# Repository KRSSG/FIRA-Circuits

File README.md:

# FIRA-Circuits
Eagle Files of FIRA Circuit

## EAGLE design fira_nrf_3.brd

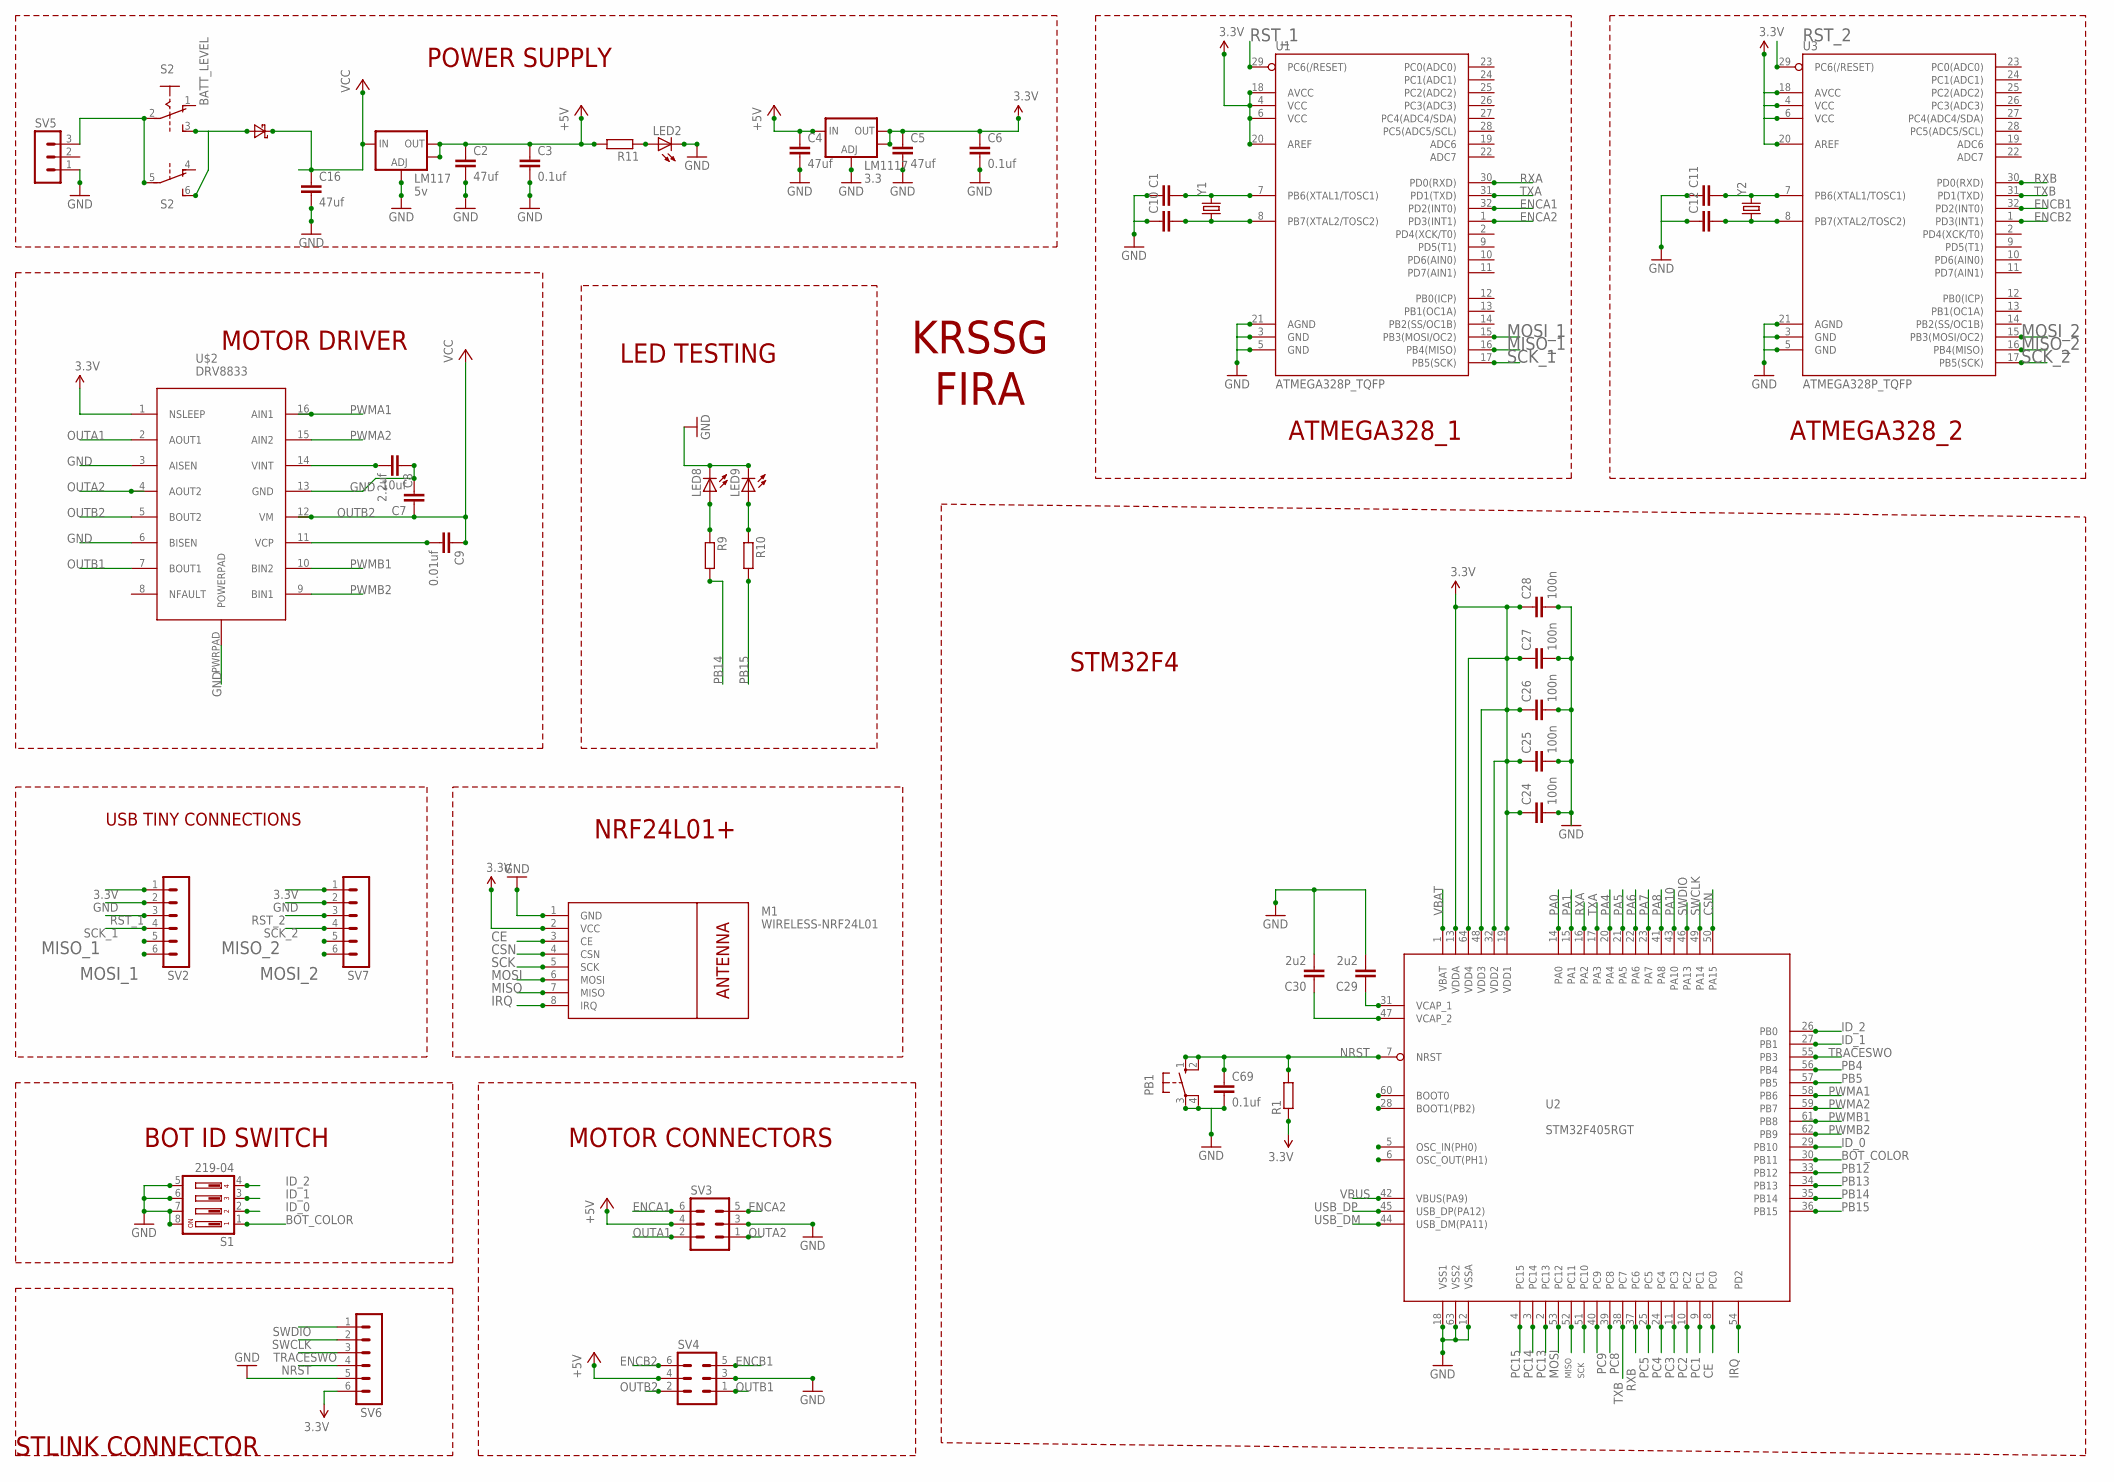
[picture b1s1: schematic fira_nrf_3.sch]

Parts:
C1, C10, C11, C12: CAP0603-CAP; 0603-CAP
C2, C4, C5, C16: 47uf; C1206
C3, C6, C69: 0.1uf; C1206
C7: 10uf; C1206
C8: 2.2uf; C1206
C9: 0.01uf; C1206
C24, C25, C26, C27, C28: 100n; 0603-CAP
C29, C30: 2u2; 0603-CAP
LED2, LED8, LED9: LEDCHIPLED_1206; CHIPLED_1206
LM117: 5v; SOT223
LM1117: 3.3; SOT223
M1: WIRELESS-NRF24L01
PB1: 10-XX; B3F-10XX
R1: R-EU_M0805; M0805
R9, R10, R11: R-EU_R1206; R1206
S1: 219-04; CTS-219-04
S2: A68-A31
SV2, SV6, SV7: MA06-1
SV3, SV4: MA03-2
SV5: MA03-1
U1, U3: ATMEGA328P_TQFP; TQFP32-08
U2: STM32F405RGT; LQFP64
U$2: DRV8833; PWP_R_PDSO_G16
VD1: IDD06SG60C; DPAK
Y1, Y2: CRYSTAL5X3; CRYSTAL-SMD-5X3

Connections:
3.3V: C5.1, C6.1, C24.1, C25.1, C26.1, C27.1, C28.1, LM1117.2 (OUT), LM1117.4 (OUT), M1.2 (VCC), R1.1, SV2.1, SV6.6, SV7.1, U1.4 (VCC), U1.6 (VCC), U1.18 (AVCC), U1.20 (AREF), U2.13 (VDDA), U2.19 (VDD1), U2.32 (VDD2), U2.48 (VDD3), U2.64 (VDD4), U3.4 (VCC), U3.6 (VCC), U3.18 (AVCC), U3.20 (AREF), U$2.1 (NSLEEP)
+5V: C2.1, C3.1, C4.1, LM117.2 (OUT), LM117.4 (OUT), LM1117.3 (IN), R11.2, SV3.4, SV4.4
BATT_LEVEL: S2.3 (S), S2.6 (S), VD1.3 (A)
BOT_COLOR: S1.1, U2.30 (PB11)
CE: M1.3 (CE), U2.8 (PC0)
CSN: M1.4 (CSN), U2.50 (PA15)
ENCA1: SV3.6, U1.32 (PD2(INT0))
ENCA2: SV3.5, U1.1 (PD3(INT1))
ENCB1: SV4.5, U3.32 (PD2(INT0))
ENCB2: SV4.6, U3.1 (PD3(INT1))
ID_0: S1.2, U2.29 (PB10)
ID_1: S1.3, U2.27 (PB1)
ID_2: S1.4, U2.26 (PB0)
IRQ: M1.8 (IRQ), U2.54 (PD2)
MISO: M1.7 (MISO), U2.52 (PC11)
MISO_1: SV2.5, U1.16 (PB4(MISO))
MISO_2: SV7.5, U3.16 (PB4(MISO))
MOSI: M1.6 (MOSI), U2.53 (PC12)
MOSI_1: SV2.6, U1.15 (PB3(MOSI/OC2))
MOSI_2: SV7.6, U3.15 (PB3(MOSI/OC2))
unnamed: LED2.A, R11.1
unnamed: LED9.A, R10.1
unnamed: C11.2, U3.7 (PB6(XTAL1/TOSC1)), Y2.3 (2)
unnamed: C8.2, U$2.14 (VINT)
unnamed: LED8.A, R9.1
unnamed: S2.2, S2.5, SV5.3
unnamed: C9.2, U$2.11 (VCP)
unnamed: C12.2, U3.8 (PB7(XTAL2/TOSC2)), Y2.1
unnamed: C29.1, U2.31 (VCAP_1)
unnamed: C30.1, U2.47 (VCAP_2)
unnamed: C1.2, U1.7 (PB6(XTAL1/TOSC1)), Y1.3 (2)
unnamed: C10.2, U1.8 (PB7(XTAL2/TOSC2)), Y1.1
NRST: C69.1, PB1.1 (S), PB1.2 (S1), R1.2, SV6.4, U2.7 (NRST)
OUTA1: SV3.2, U$2.2 (AOUT1)
OUTA2: SV3.1, U$2.4 (AOUT2)
OUTB1: SV4.1, U$2.7 (BOUT1)
OUTB2: SV4.2, U$2.5 (BOUT2)
PA0: U2.14 (PA0)
PA1: U2.15 (PA1)
PA4: U2.20 (PA4)
PA5: U2.21 (PA5)
PA6: U2.22 (PA6)
PA7: U2.23 (PA7)
PA8: U2.41 (PA8)
PA10: U2.43 (PA10)
PB4: U2.56 (PB4)
PB5: U2.57 (PB5)
PB12: U2.33 (PB12)
PB13: U2.34 (PB13)
PB14: R9.2, U2.35 (PB14)
PB15: R10.2, U2.36 (PB15)
PC1: U2.9 (PC1)
PC2: U2.10 (PC2)
PC3: U2.11 (PC3)
PC4: U2.24 (PC4)
PC5: U2.25 (PC5)
PC8: U2.39 (PC8)
PC9: U2.40 (PC9)
PC13: U2.2 (PC13)
PC14: U2.3 (PC14)
PC15: U2.4 (PC15)
PWMA1: U2.58 (PB6), U$2.16 (AIN1)
PWMA2: U2.59 (PB7), U$2.15 (AIN2)
PWMB1: U2.61 (PB8), U$2.10 (BIN2)
PWMB2: U2.62 (PB9), U$2.9 (BIN1)
RST_1: SV2.3, U1.29 (PC6(/RESET))
RST_2: SV7.3, U3.29 (PC6(/RESET))
RXA: U1.30 (PD0(RXD)), U2.16 (PA2)
RXB: U2.37 (PC6), U3.30 (PD0(RXD))
SCK: M1.5 (SCK), U2.51 (PC10)
SCK_1: SV2.4, U1.17 (PB5(SCK))
SCK_2: SV7.4, U3.17 (PB5(SCK))
SWCLK: SV6.2, U2.49 (PA14)
SWDIO: SV6.1, U2.46 (PA13)
TRACESWO: SV6.3, U2.55 (PB3)
TXA: U1.31 (PD1(TXD)), U2.17 (PA3)
TXB: U2.38 (PC7), U3.31 (PD1(TXD))
USB_DM: U2.44 (USB_DM(PA11))
USB_DP: U2.45 (USB_DP(PA12))
VBAT: U2.1 (VBAT)
VBUS: U2.42 (VBUS(PA9))
VCC: C7.1, C9.1, C16.1, LM117.3 (IN), U$2.12 (VM), VD1.2 (C)

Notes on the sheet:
BOT ID SWITCH
MOTOR CONNECTORS
MOTOR DRIVER
STM32F4
POWER SUPPLY
STLINK CONNECTOR
LED TESTING
ATMEGA328_1
ATMEGA328_2
KRSSG
FIRA
NRF24L01+
USB TINY CONNECTIONS

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
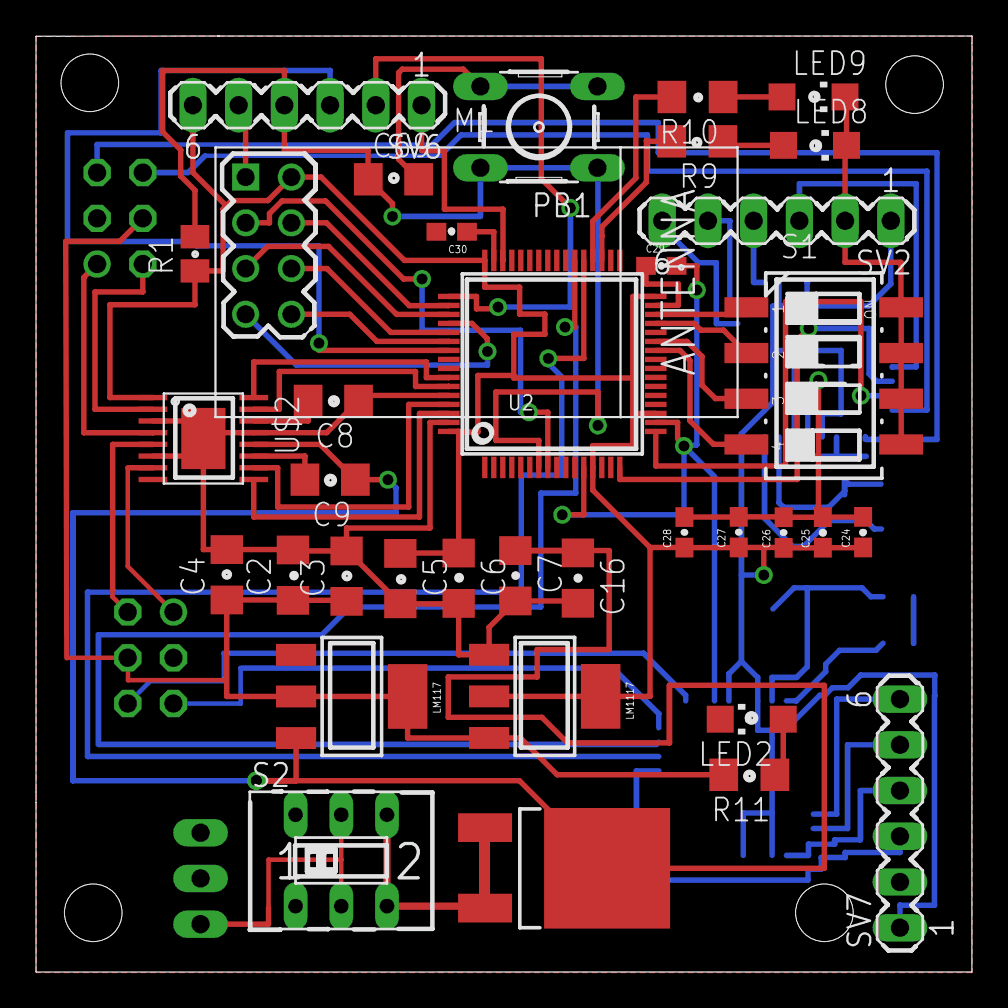
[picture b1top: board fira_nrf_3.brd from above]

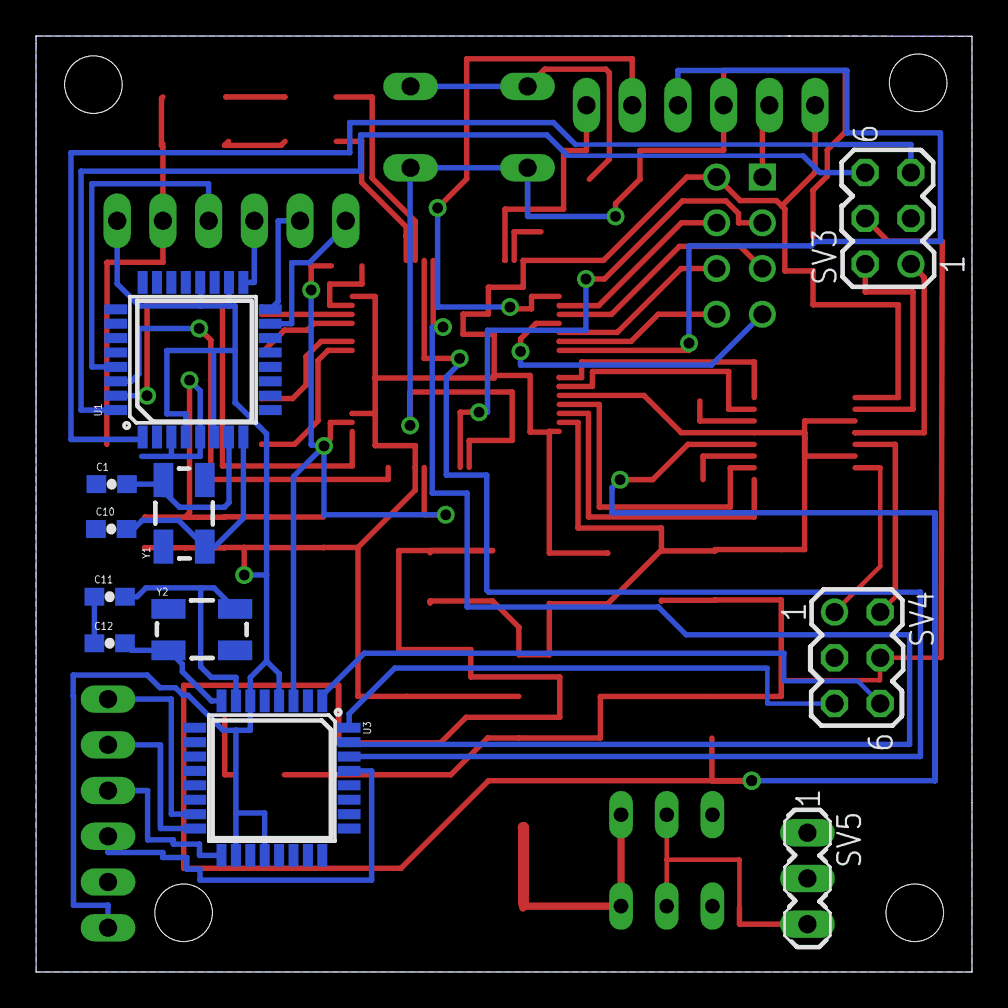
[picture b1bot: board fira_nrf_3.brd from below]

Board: 2 copper layers, 52.0 x 52.0 mm, 47 parts (11 on the bottom side), 57 nets.

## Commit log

2018-08-26 init
2018-08-26 boot 0 issue solved
2018-12-22 Updated Dimensions
2018-12-22 version

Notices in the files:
parts and their libraries:
SparkFun-Passives: Licensing: Creative Commons ShareAlike 4.0 International - https://creativecommons.org/licenses/by-sa/4.0
diy-modules: Released under the Creative Commons Attribution 4.0 International License: http://creativecommons.org/licenses/by/4.0
